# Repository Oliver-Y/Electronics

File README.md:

# Electronics
# Attiny 84

## Bit Shifting: 

#### Set a bit(output)
byte |= (1 << pin_number) 
byte = byte | (1<< pin_number) 
10000000
or: doesn’t overwrite. 
because if u compare it as u do as multiplication 0 and a 1 will give out a high and 1 and 1 will still give a high yaya. 

#### Clear a bit(input) 
and: Overwrites (for 0)
byte &= ~(1<<pin_number) 
 ~: Flip all the bits

#### Checking a bit
Use and. Value shifted over to the rite(bit u wanna check)
and one. 
if (!(byte1 >> 2) & 1  == (old_byte1 >>2) &1)

## Pushing Firmware
Use "Make" to compile new .hex and .out
Make File contains all the commands in terminal: 
If like there are different libraries: (aka if I switch a different type of chip) *make clean*. 
Clean it to make completely new hex and out files--> Command: make clean
Make program-usbtiny (Or whatever programmer you're using) → to take the firmware and put it into the microbit.

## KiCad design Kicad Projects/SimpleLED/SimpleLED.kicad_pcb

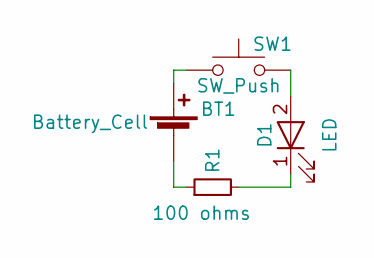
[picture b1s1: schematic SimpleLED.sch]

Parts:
BT1: Battery_Cell; bu-2032-1
D1: LED; LED_D5.0mm
R1: 100 ohms; R_Axial_DIN0207_L6.3mm_D2.5mm_P10.16mm_Horizontal
SW1: SW_Push; SW_PUSH-12mm_Wuerth-430476085716

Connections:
unnamed: BT1.1 (+), SW1.1
unnamed: BT1.2 (-), R1.1
unnamed: D1.1 (K), R1.2
unnamed: D1.2 (A), SW1.2

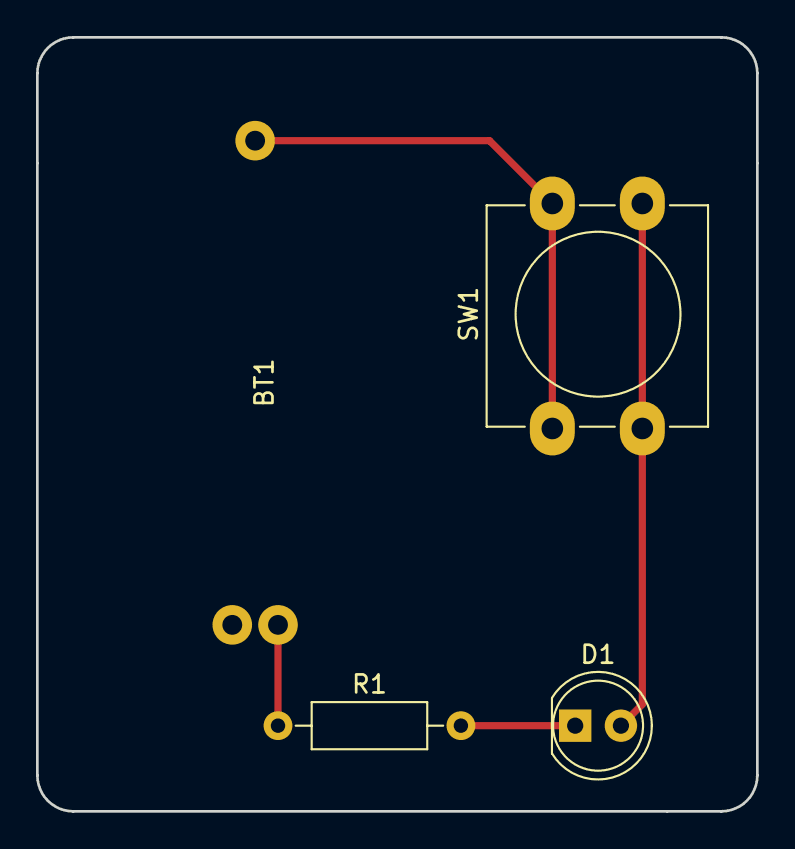
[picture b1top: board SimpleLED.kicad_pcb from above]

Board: 2 copper layers, 40.0 x 43.0 mm, 4 parts (0 on the bottom side), 4 nets.

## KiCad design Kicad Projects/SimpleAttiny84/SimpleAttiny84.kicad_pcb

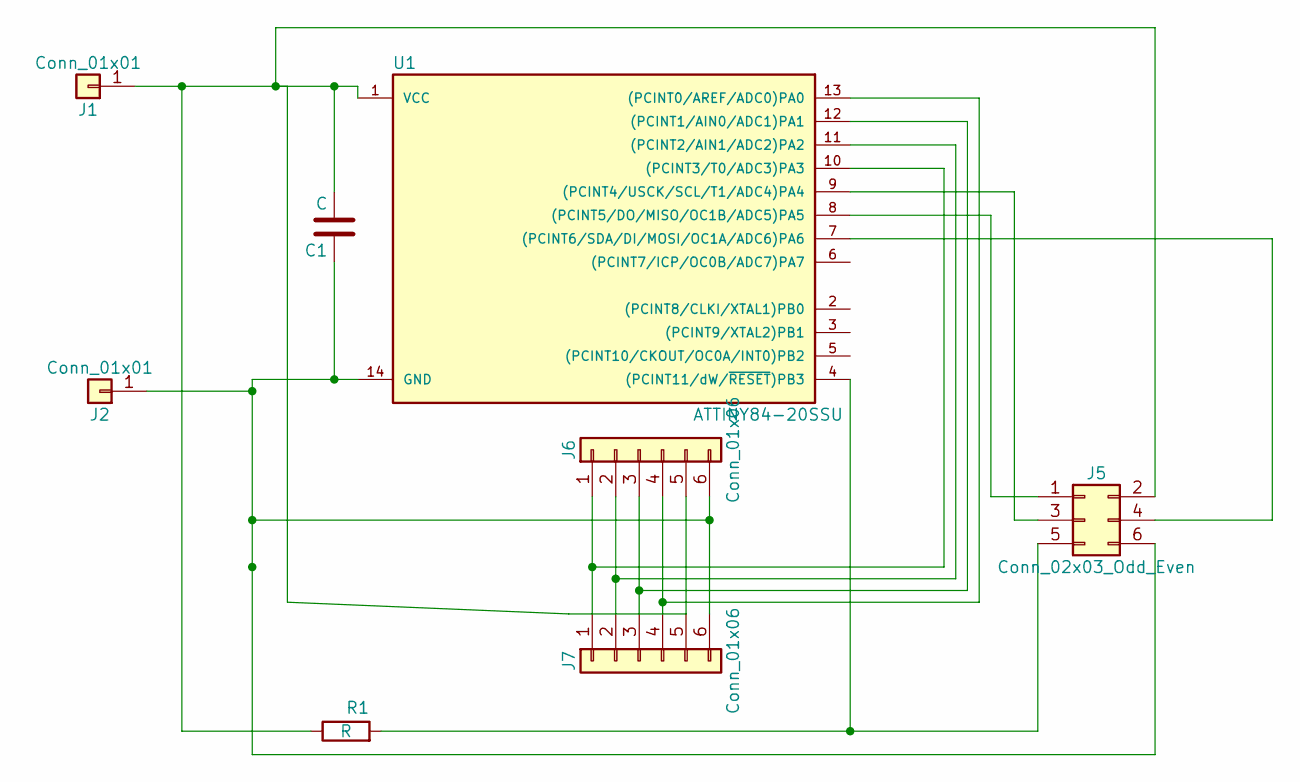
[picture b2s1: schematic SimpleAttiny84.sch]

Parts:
C1: C; C_1206_HandSoldering
J1, J2: Conn_01x01; Pin_Header_Straight_1x01_Pitch2.54mm
J5: Conn_02x03_Odd_Even; Pin_Header_Straight_2x03_Pitch2.54mm_SMD
J6, J7: Conn_01x06; Pin_Header_Straight_1x06_Pitch2.54mm
R1: R; R_1206_HandSoldering
U1: ATTINY84-20SSU; SOIC-14_3.9x8.7mm_Pitch1.27mm

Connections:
unnamed: C1.1, J2.1, J5.6, J6.6, J7.6, U1.14 (GND)
unnamed: C1.2, J1.1, J5.2, J6.5, J7.5, R1.1, U1.1 (VCC)
unnamed: J5.1, U1.8 ((PCINT5/DO/MISO/OC1B/ADC5)PA5)
unnamed: J5.3, U1.9 ((PCINT4/USCK/SCL/T1/ADC4)PA4)
unnamed: J5.4, U1.7 ((PCINT6/SDA/DI/MOSI/OC1A/ADC6)PA6)
unnamed: J5.5, R1.2, U1.4 ((PCINT11/dW/~RESET~)PB3)
unnamed: J6.1, J7.1, U1.10 ((PCINT3/T0/ADC3)PA3)
unnamed: J6.2, J7.2, U1.11 ((PCINT2/AIN1/ADC2)PA2)
unnamed: J6.3, J7.3, U1.12 ((PCINT1/AIN0/ADC1)PA1)
unnamed: J6.4, J7.4, U1.13 ((PCINT0/AREF/ADC0)PA0)

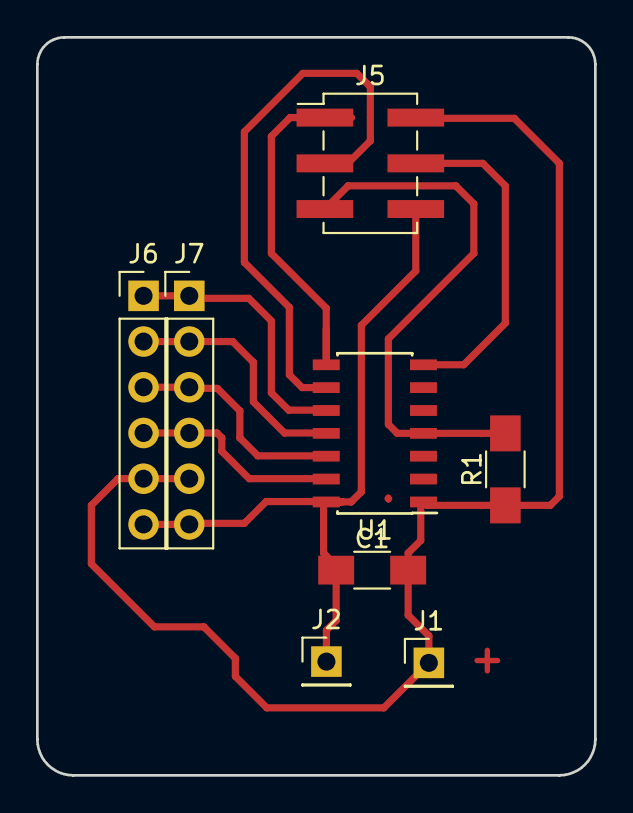
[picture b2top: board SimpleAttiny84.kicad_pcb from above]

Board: 2 copper layers, 31.0 x 41.0 mm, 8 parts (0 on the bottom side), 10 nets.

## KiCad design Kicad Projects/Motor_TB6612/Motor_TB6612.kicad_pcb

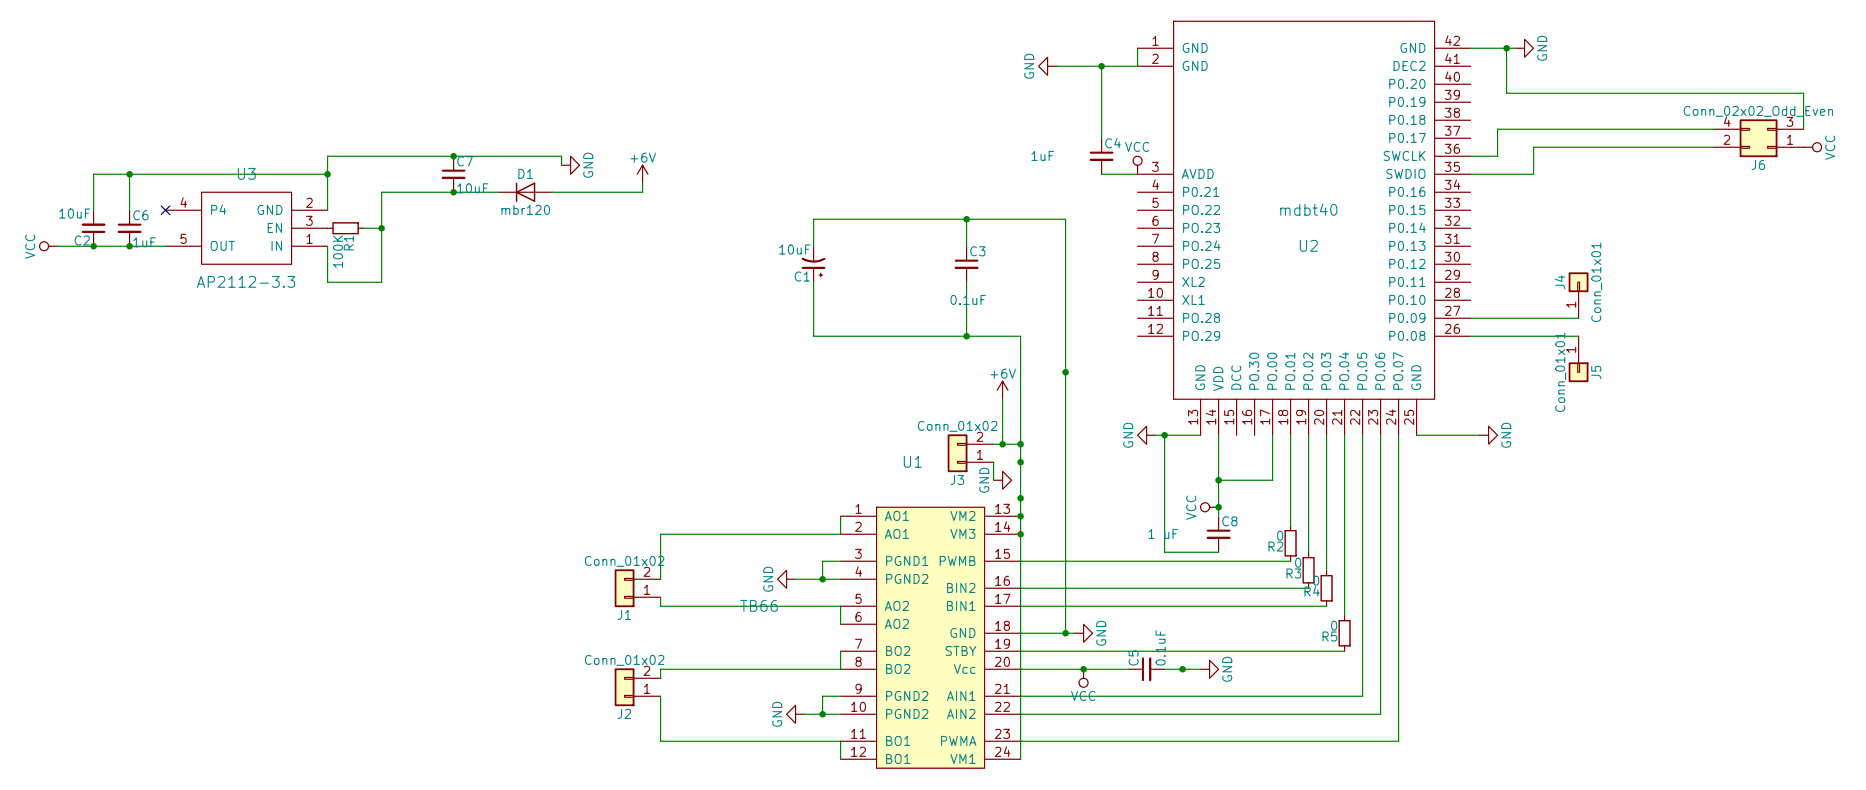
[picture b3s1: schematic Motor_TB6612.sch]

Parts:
C1: 10uF; CP_Tantalum_Case-B_EIA-3528-21_Reflow
C2, C7: 10uF; C_1206
C3, C5: 0.1uF; C_1206
C4, C6: 1uF; C_1206
C8: 1 uF; C_1206
D1: mbr120; D_SOD-123F
J1, J2, J3: Conn_01x02; Pin_Header_Straight_1x02_Pitch2.54mm
J4, J5: Conn_01x01; Pin_Header_Straight_1x01_Pitch2.54mm
J6: Conn_02x02_Odd_Even; Pin_Header_Straight_2x02_Pitch2.54mm_SMD
R1: 100K; R_1206
R2, R3, R4, R5: 0; Jumper_5.3mm
U1: TB66; TB6612FNG
U2: mdbt40; mdbt40_hand_solder
U3: AP2112-3.3

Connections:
+6V: C1.1, C3.2, D1.2 (A), J3.2, U1.13 (VM2), U1.14 (VM3), U1.24 (VM1)
GND: C1.2, C2.2, C3.1, C4.1, C5.2, C6.1, C7.1, C8.2, J3.1, J6.3, U1.3 (PGND1), U1.4 (PGND2), U1.9 (PGND2), U1.10 (PGND2), U1.18 (GND), U2.1 (GND), U2.2 (GND), U2.13 (GND), U2.25 (GND), U2.42 (GND), U3.2 (GND)
unnamed: C7.2, D1.1 (K), R1.1, U3.1 (IN)
unnamed: J1.1, U1.5 (AO2), U1.6 (AO2)
unnamed: J1.2, U1.1 (AO1), U1.2 (AO1)
unnamed: J2.1, U1.11 (BO1), U1.12 (BO1)
unnamed: J2.2, U1.7 (BO2), U1.8 (BO2)
unnamed: J4.1, U2.27 (P0.09)
unnamed: J5.1, U2.26 (P0.08)
unnamed: J6.2, U2.35 (SWDIO)
unnamed: J6.4, U2.36 (SWCLK)
unnamed: R1.2, U3.3 (EN)
unnamed: R2.1, U1.15 (PWMB)
unnamed: R2.2, U2.18 (PO.01)
unnamed: R3.1, U1.16 (BIN2)
unnamed: R3.2, U2.19 (PO.02)
unnamed: R4.1, U1.17 (BIN1)
unnamed: R4.2, U2.20 (PO.03)
unnamed: R5.1, U1.19 (STBY)
unnamed: R5.2, U2.21 (PO.04)
unnamed: U1.21 (AIN1), U2.22 (PO.05)
unnamed: U1.22 (AIN2), U2.23 (PO.06)
unnamed: U1.23 (PWMA), U2.24 (PO.07)
VCC: C2.1, C4.2, C5.1, C6.2, C8.1, J6.1, U1.20 (Vcc), U2.3 (AVDD), U2.14 (VDD), U2.17 (PO.00), U3.5 (OUT)

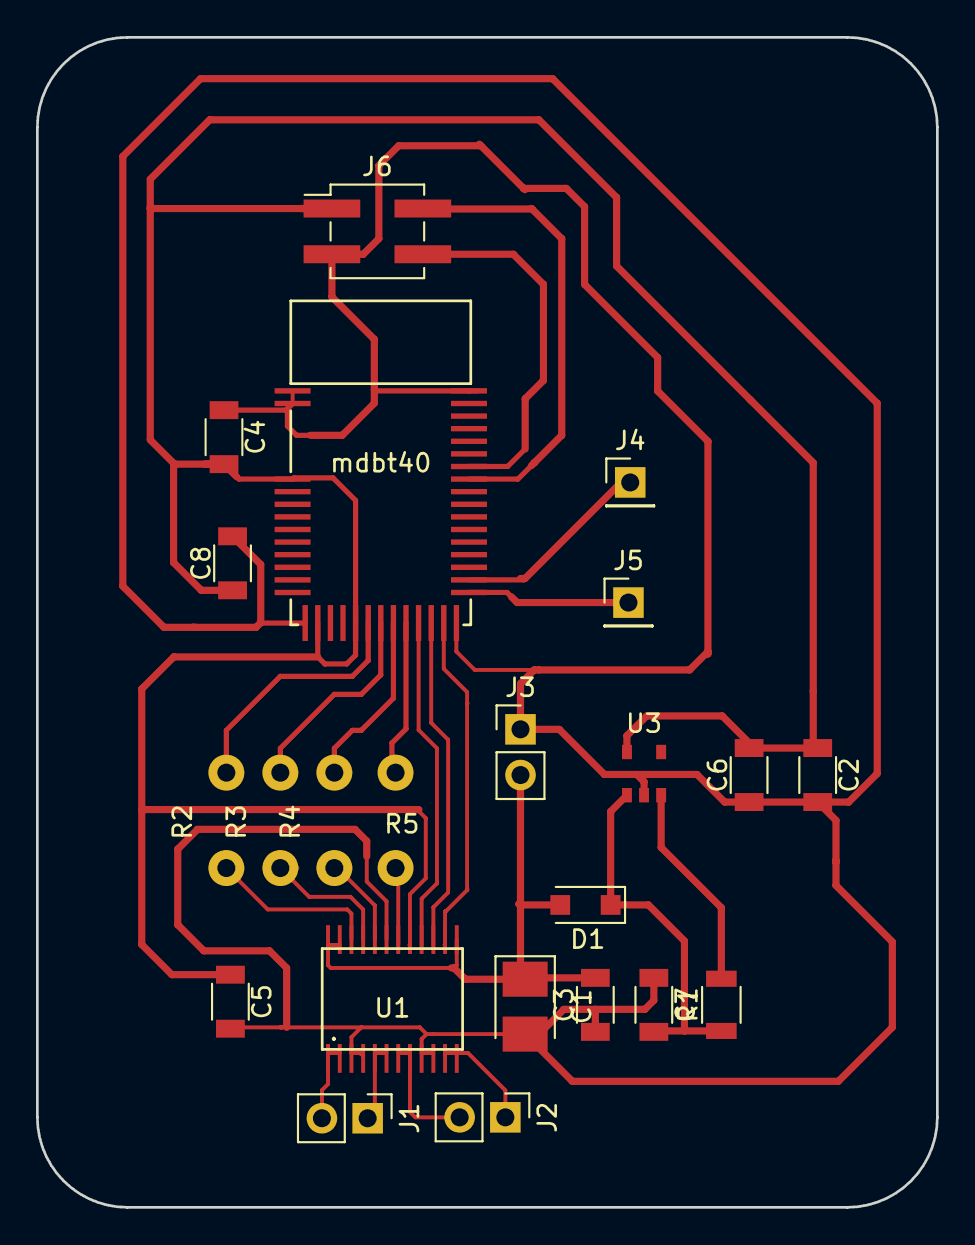
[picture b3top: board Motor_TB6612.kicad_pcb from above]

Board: 2 copper layers, 50.0 x 65.0 mm, 23 parts (0 on the bottom side), 24 nets.

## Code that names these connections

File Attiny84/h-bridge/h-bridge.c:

//
//
// hello.ftdi.44.echo.c
//
// 115200 baud FTDI character echo, with flash string
//
// set lfuse to 0x5E for 20 MHz xtal
//
// Neil Gershenfeld
// 12/8/10
//
// (c) Massachusetts Institute of Technology 2010
// This work may be reproduced, modified, distributed,
// performed, and displayed for any purpose. Copyright is
// retained and must be preserved. The work is provided
// as is; no warranty is provided, and users accept all
// liability.
//

#include <avr/io.h>
#include <util/delay.h>
#include <avr/pgmspace.h>


int main(void) {
  uint8_t m_forward, m_back;
   //
   // set clock divider to /1
   //
   CLKPR = (1 << CLKPCE);
   CLKPR = (0 << CLKPS3) | (0 << CLKPS2) | (0 << CLKPS1) | (0 << CLKPS0);
   //Setting Direciotns
   PORTA = (1<<PA1) | (1<<PA0);
   DDRA = (1<<DDRA4) | (1<<DDRA3);
   while (1) {
     //Toggling sleep command
     //Toggling PORTX Registor
     //PINA = (1<<PINA0);
    m_forward = (PINA >> PINA0) & 1;
    m_backward = (PINA >> PINA1) & 1;
    //Both Low (which means both buttons r pressed since pull up inverts it)
    if (!m_forward && !m_backward)
    {
      //clear the both pins
      PORTA &= ~((1<<PA1) | (1<<PA0));

    }
    //One High One Low
    else if (m_forward){
      //FIRST MAKE SURE ONE IS LOW
      PORTA &= ~(1<<PA3);
      PORTA |= (1<<PA4);
    }

    else if(m_backward){
      //FIRST MAKE SURE ONE IS LOW
      PORTA &= ~(1<<PA4);
      PORTA |= (1<<PA3);
    }
    //Both high, which is the default resting state. and I want the motor to turn off.
    else{
      PORTA &= ~((1<<PA1) | (1<<PA0));
    }

   }
 }

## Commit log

2018-07-20 first microcontroller project
2018-07-20 Added webpage
2018-07-28 styling for page
2018-09-13 Missing Video
2018-09-13 added pics
2018-10-19 random commit
